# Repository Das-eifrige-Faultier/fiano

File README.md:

# Fiano

A individual ergonomic split keyboard, so typing becomes easy as playing the piano...

---

## This is an explanation
Everything in here is markdown

---

## Code to create a pcb

```zsh
cd fiano

ergogen .

```
---

Und hier noch eine Tabelle:

| Funktion  | Check |
| --------- | ----- |
| Bluetooth |  ✓   |

---

Test

~~~graph-easy --as=boxart
[ A ] - to -> [ B ]
~~~

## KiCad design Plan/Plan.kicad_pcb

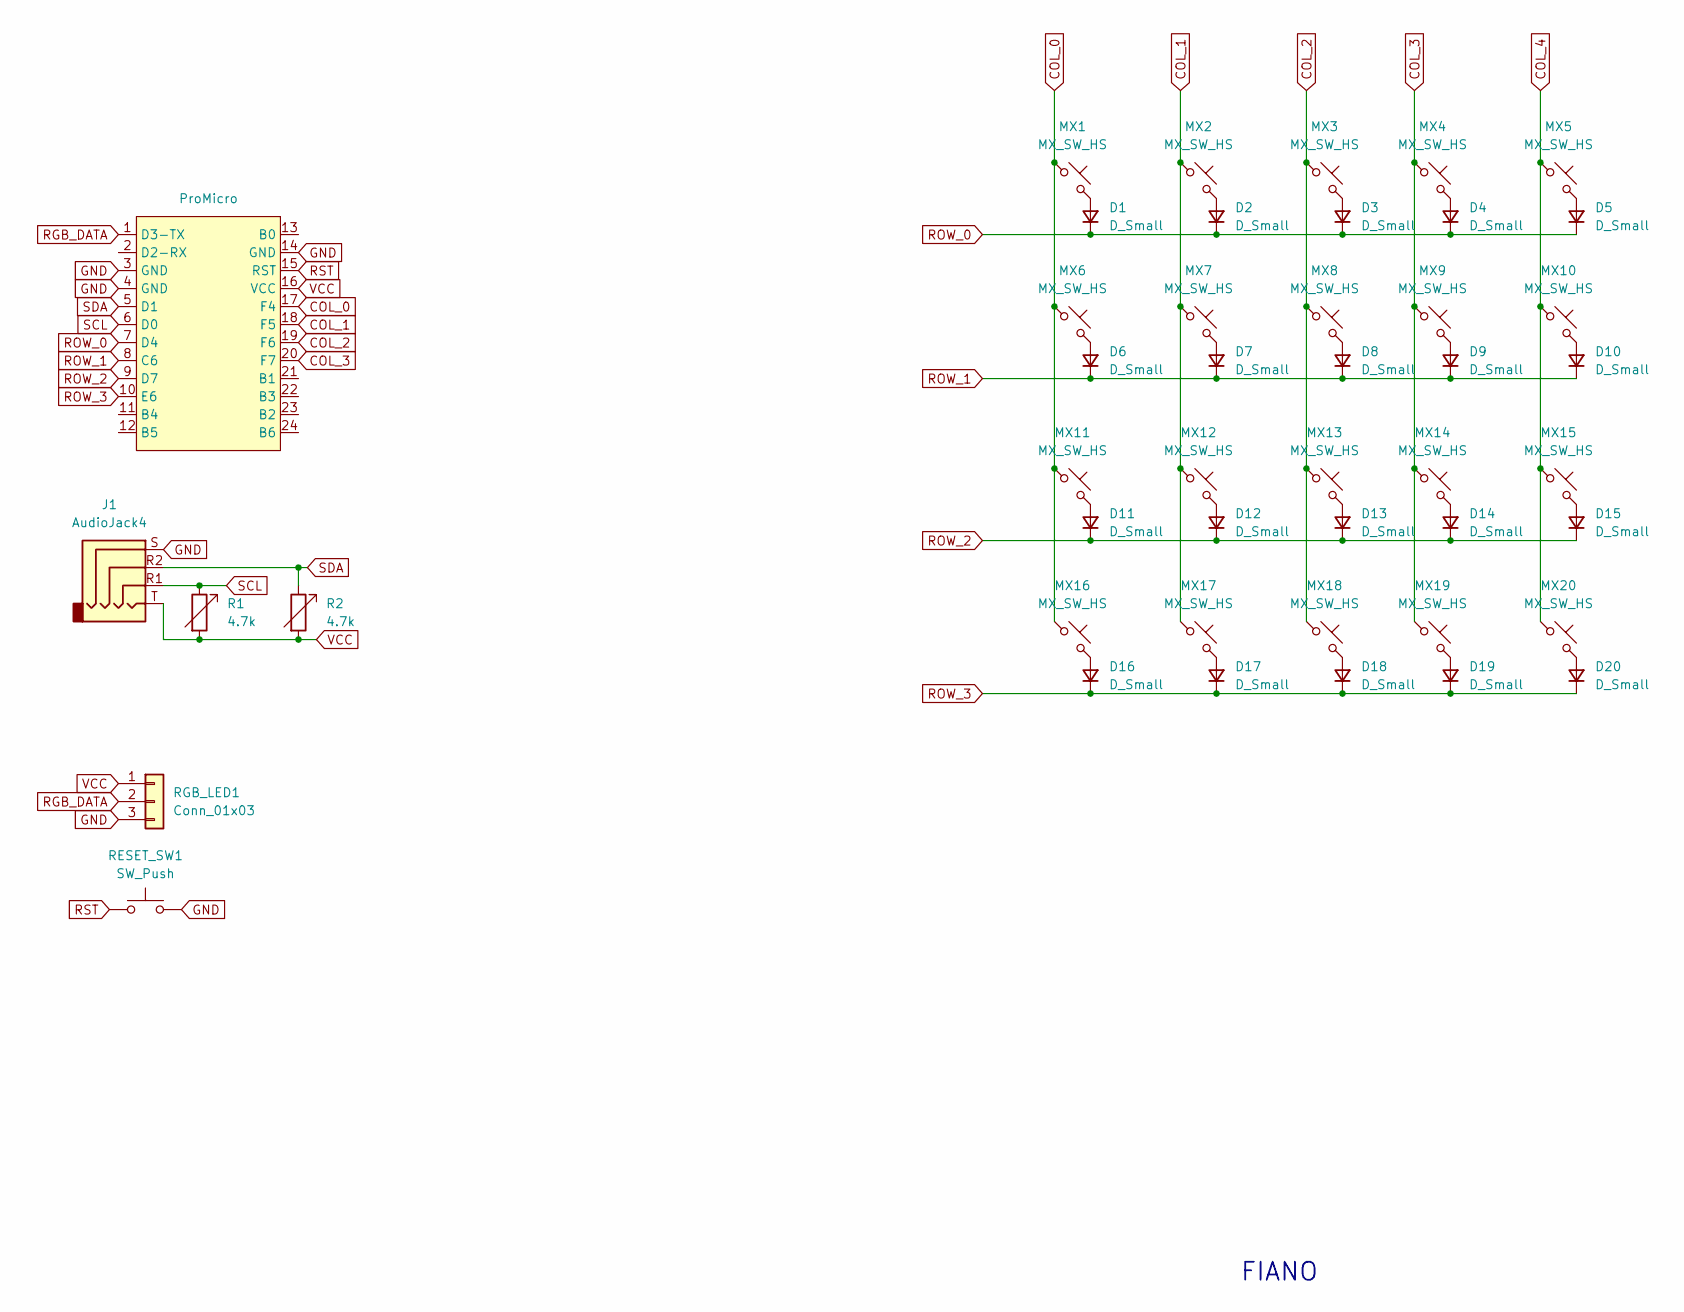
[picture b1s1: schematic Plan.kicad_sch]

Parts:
D1, D2, D3, D4, D5, D6, D7, D8, D9, D10, D12, D13, D14, D15, D16, D17, D18, D19, D20: D_Small; D_SOD-123
D11: D_Small; Diode-hybrid-3pad
J1: AudioJack4; CON_MJ-4PP-9
MX1, MX2, MX3, MX4, MX5, MX6, MX7, MX8, MX9, MX10, MX11, MX12, MX13, MX14, MX15, MX16, MX17, MX18, MX19, MX20: MX_SW_HS; SW_MX_1u
R1, R2: 4.7k
RESET_SW1: SW_Push
RGB_LED1: Conn_01x03
U2: ProMicro; ProMicro_USBup

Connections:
COL_0: MX1.1, MX6.1, MX11.1, MX16.1, U2.17 (F4)
COL_1: MX2.1, MX7.1, MX12.1, MX17.1, U2.18 (F5)
COL_2: MX3.1, MX8.1, MX13.1, MX18.1, U2.19 (F6)
COL_3: MX4.1, MX9.1, MX14.1, MX19.1, U2.20 (F7)
COL_4: MX5.1, MX10.1, MX15.1, MX20.1
GND: J1.S, RESET_SW1.2, RGB_LED1.3, U2.3 (GND), U2.4 (GND), U2.14 (GND)
unnamed: D1.2 (A), MX1.2
unnamed: D2.2 (A), MX2.2
unnamed: D3.2 (A), MX3.2
unnamed: D4.2 (A), MX4.2
unnamed: D5.2 (A), MX5.2
unnamed: D6.2 (A), MX6.2
unnamed: D7.2 (A), MX7.2
unnamed: D8.2 (A), MX8.2
unnamed: D9.2 (A), MX9.2
unnamed: D10.2 (A), MX10.2
unnamed: D11.2 (A), MX11.2
unnamed: D12.2 (A), MX12.2
unnamed: D13.2 (A), MX13.2
unnamed: D14.2 (A), MX14.2
unnamed: D15.2 (A), MX15.2
unnamed: D16.2 (A), MX16.2
unnamed: D17.2 (A), MX17.2
unnamed: D18.2 (A), MX18.2
unnamed: D19.2 (A), MX19.2
unnamed: D20.2 (A), MX20.2
RGB_DATA: RGB_LED1.2, U2.1 (D3-TX)
ROW_0: D1.1 (K), D2.1 (K), D3.1 (K), D4.1 (K), D5.1 (K), U2.7 (D4)
ROW_1: D6.1 (K), D7.1 (K), D8.1 (K), D9.1 (K), D10.1 (K), U2.8 (C6)
ROW_2: D11.1 (K), D12.1 (K), D13.1 (K), D14.1 (K), D15.1 (K), U2.9 (D7)
ROW_3: D16.1 (K), D17.1 (K), D18.1 (K), D19.1 (K), D20.1 (K), U2.10 (E6)
RST: RESET_SW1.1, U2.15 (RST)
SCL: J1.R1, R1.1, U2.6 (D0)
SDA: J1.R2, R2.1, U2.5 (D1)
VCC: J1.T, R1.2, R2.2, RGB_LED1.1, U2.16 (VCC)

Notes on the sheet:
FIANO

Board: 2 copper layers, 42 parts (0 on the bottom side), 33 nets, no tracks yet.

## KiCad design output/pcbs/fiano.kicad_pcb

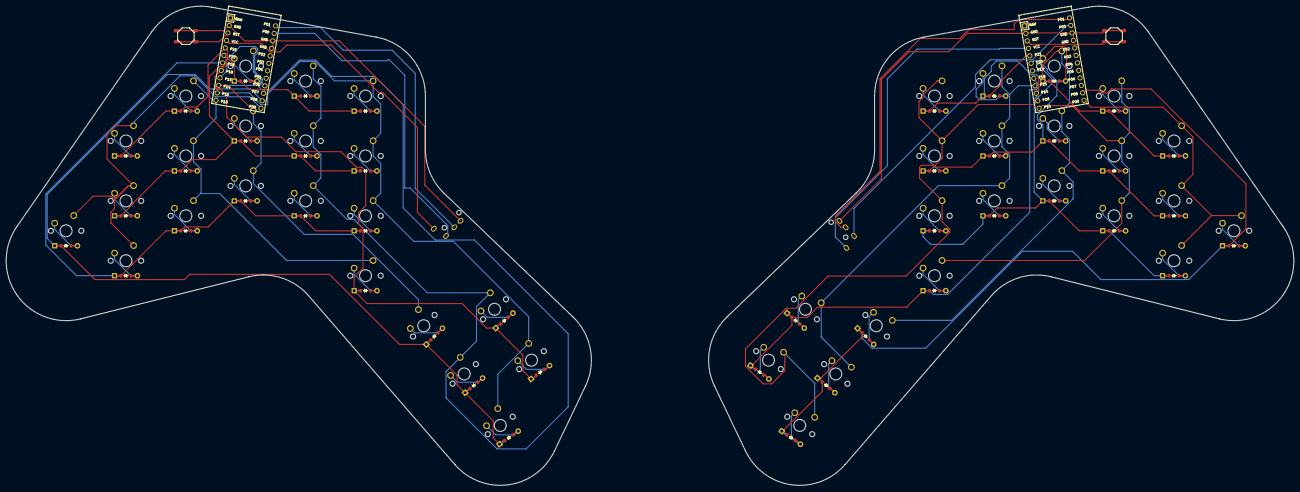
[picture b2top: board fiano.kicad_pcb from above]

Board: 2 copper layers, 430.0 x 160.0 mm, 94 parts (0 on the bottom side), 74 nets.

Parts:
B1, B2: SW_TACT_ALPS_SKQGABE010
D1, D2, D3, D4, D5, D6, D7, D8, D9, D10, D11, D12, D13, D14, D15, D16, D17, D18, D19, D20, D21, D22, D23, D24, D25, D26, D27, D28, D29, D30, D31, D32, D33, D34, D35, D36, D37, D38, D39, D40, D41, D42, D43, D44: ComboDiode
MCU1, MCU2: ProMicro
S1, S2, S3, S4, S5, S6, S7, S8, S9, S10, S11, S12, S13, S14, S15, S16, S17, S18, S19, S20, S21, S22, S23, S24, S25, S26, S27, S28, S29, S30, S31, S32, S33, S34, S35, S36, S37, S38, S39, S40, S41, S42, S43, S44: MX
TRRS1, TRRS2: TRRS-PJ-320A-dual

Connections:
GNDL: B1.1, MCU1.2, MCU1.15, MCU1.16, TRRS1.4
GNDR: B2.1, MCU2.2, MCU2.15, MCU2.16, TRRS2.4
L0: MCU1.14, TRRS1.2
L1: MCU1.13, TRRS1.3
L8: D1.1, D18.1, D19.1, D20.1, MCU1.23
L9: MCU1.24, S1.1, S2.1, S3.1, S4.1
L10: MCU1.12, S5.1, S6.1, S7.1, S14.1
L14: MCU1.10, S8.1, S9.1, S10.1, S20.1
L15: MCU1.9, S11.1, S12.1, S13.1, S19.1, S22.1
L16: MCU1.11, S15.1, S16.1, S17.1, S18.1, S21.1
L18: D14.1, D21.1, D22.1, MCU1.8
L19: D2.1, D5.1, D8.1, D11.1, D15.1, MCU1.7
L20: D3.1, D6.1, D9.1, D12.1, D16.1, MCU1.6
L21: D4.1, D7.1, D10.1, D13.1, D17.1, MCU1.5
R0: MCU2.14, TRRS2.2
R1: MCU2.13, TRRS2.3
R8: D23.1, D40.1, D41.1, D42.1, MCU2.23
R9: MCU2.24, S23.1, S24.1, S25.1, S26.1
R10: MCU2.12, S27.1, S28.1, S29.1, S36.1
R14: MCU2.10, S30.1, S31.1, S32.1, S42.1
R15: MCU2.9, S33.1, S34.1, S35.1, S41.1, S44.1
R16: MCU2.11, S37.1, S38.1, S39.1, S40.1, S43.1
R18: D36.1, D43.1, D44.1, MCU2.8
R19: D24.1, D27.1, D30.1, D33.1, D37.1, MCU2.7
R20: D25.1, D28.1, D31.1, D34.1, D38.1, MCU2.6
R21: D26.1, D29.1, D32.1, D35.1, D39.1, MCU2.5
RSTL: B1.2, MCU1.3
RSTR: B2.2, MCU2.3
VCCL: MCU1.4, TRRS1.1
VCCR: MCU2.4, TRRS2.1
index_home: D11.2, S11.2
index_hometop: D12.2, S12.2
index_top: D13.2, S13.2
inner_1: D18.2, S18.2
inner_2: D19.2, S19.2
inner_3: D20.2, S20.2
inner_bottom: D14.2, S14.2
inner_home: D15.2, S15.2
inner_hometop: D16.2, S16.2
inner_top: D17.2, S17.2
middle_home: D8.2, S8.2
middle_hometop: D9.2, S9.2
middle_top: D10.2, S10.2
mirror_index_home: D33.2, S33.2
mirror_index_hometop: D34.2, S34.2
mirror_index_top: D35.2, S35.2
mirror_inner_1: D40.2, S40.2
mirror_inner_2: D41.2, S41.2
mirror_inner_3: D42.2, S42.2
mirror_inner_bottom: D36.2, S36.2
mirror_inner_home: D37.2, S37.2
mirror_inner_hometop: D38.2, S38.2
mirror_inner_top: D39.2, S39.2
mirror_middle_home: D30.2, S30.2
mirror_middle_hometop: D31.2, S31.2
mirror_middle_top: D32.2, S32.2
mirror_outer_1: D43.2, S43.2
mirror_outer_2: D44.2, S44.2
mirror_pinky_bottom: D24.2, S24.2
mirror_pinky_home: D25.2, S25.2
mirror_pinky_hometop: D26.2, S26.2
mirror_prepinky_home: D23.2, S23.2
mirror_ring_home: D27.2, S27.2
mirror_ring_hometop: D28.2, S28.2
mirror_ring_top: D29.2, S29.2
outer_1: D21.2, S21.2
outer_2: D22.2, S22.2
pinky_bottom: D2.2, S2.2
pinky_home: D3.2, S3.2
pinky_hometop: D4.2, S4.2
prepinky_home: D1.2, S1.2
ring_home: D5.2, S5.2
ring_hometop: D6.2, S6.2
ring_top: D7.2, S7.2

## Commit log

2024-11-13 initial setup and input.yaml with key positions and outlines
2024-11-13 deleted old data
2024-11-13 added gitignore
2024-11-13 modified outlines
2024-11-15 modified pcb
2024-12-17 wired pcb
2025-05-31 added 3d parts and drafts
